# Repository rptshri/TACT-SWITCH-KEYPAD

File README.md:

# TACT-SWITCH-KEYPAD
KEYPAD USING TACT SWITCH A EAGLE SCHEMATICS AND BOARD,

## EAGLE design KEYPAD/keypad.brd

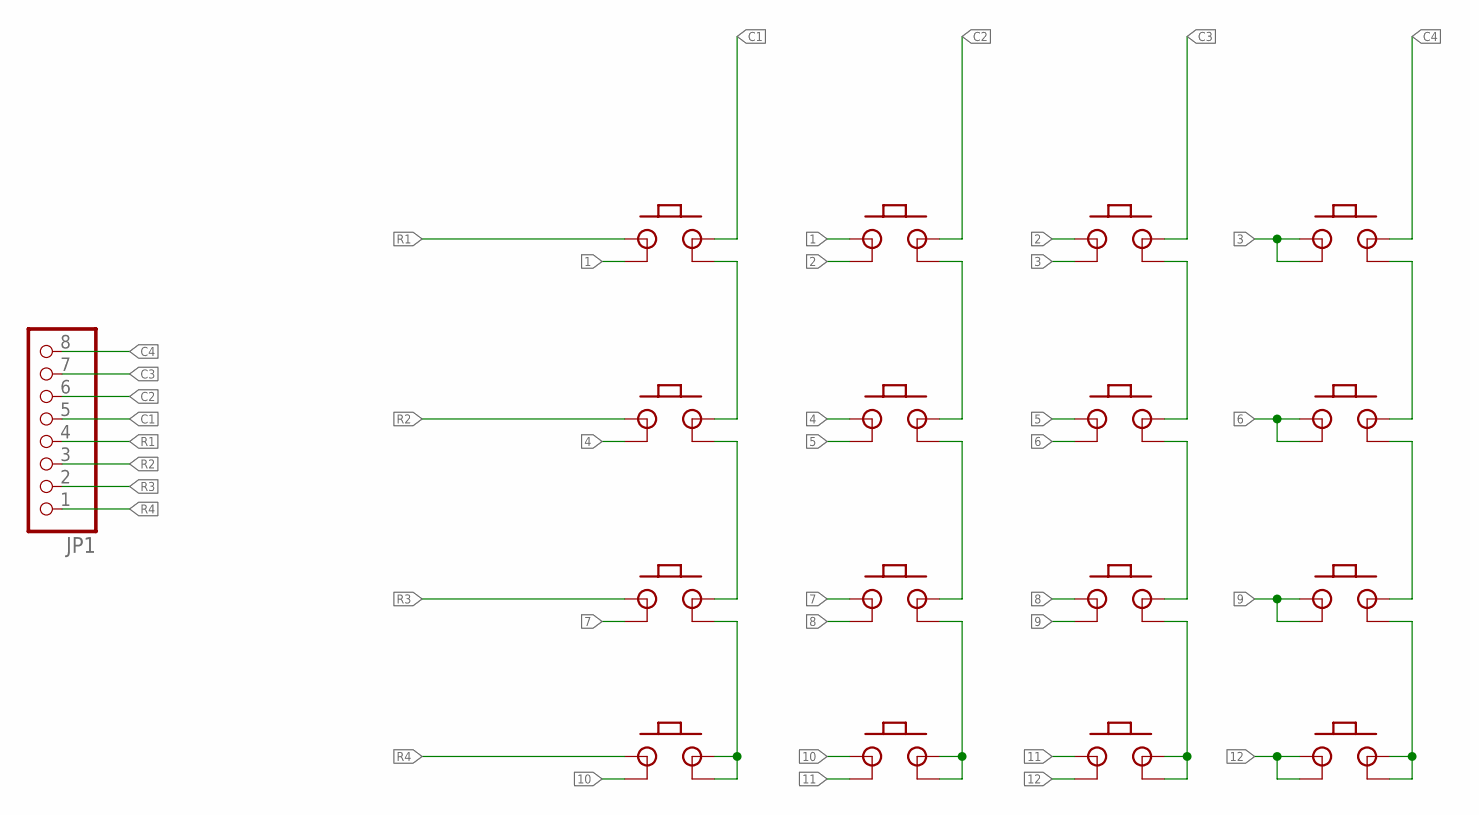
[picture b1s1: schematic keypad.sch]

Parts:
JP1: PINHD-1X8; 1X08
PB1, PB2, PB3, PB4, PB5, PB6, PB7, PB8, PB9, PB10, PB11, PB12, PB13, PB14, PB15, PB16: TACTSW

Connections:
1: PB1.P$2, PB2.P$1
2: PB2.P$2, PB3.P$1
3: PB3.P$2, PB4.P$1, PB4.P$2
4: PB5.P$2, PB6.P$1
5: PB6.P$2, PB7.P$1
6: PB7.P$2, PB8.P$1, PB8.P$2
7: PB9.P$2, PB10.P$1
8: PB10.P$2, PB11.P$1
9: PB7.P$4, PB11.P$2, PB11.P$3, PB12.P$1, PB12.P$2
10: PB13.P$2, PB14.P$1
11: PB14.P$2, PB15.P$1
12: PB15.P$2, PB16.P$1, PB16.P$2
C1: JP1.5, PB1.P$3
C2: JP1.6, PB2.P$3
C3: JP1.7, PB3.P$3
C4: JP1.8, PB4.P$3
unnamed: PB1.P$4, PB5.P$3
unnamed: PB5.P$4, PB9.P$3
unnamed: PB9.P$4, PB13.P$3, PB13.P$4
unnamed: PB2.P$4, PB6.P$3
unnamed: PB6.P$4, PB10.P$3
unnamed: PB10.P$4, PB14.P$3, PB14.P$4
unnamed: PB3.P$4, PB7.P$3
unnamed: PB11.P$4, PB15.P$3, PB15.P$4
unnamed: PB4.P$4, PB8.P$3
unnamed: PB8.P$4, PB12.P$3
unnamed: PB12.P$4, PB16.P$3, PB16.P$4
R1: JP1.4, PB1.P$1
R2: JP1.3, PB5.P$1
R3: JP1.2, PB9.P$1
R4: JP1.1, PB13.P$1

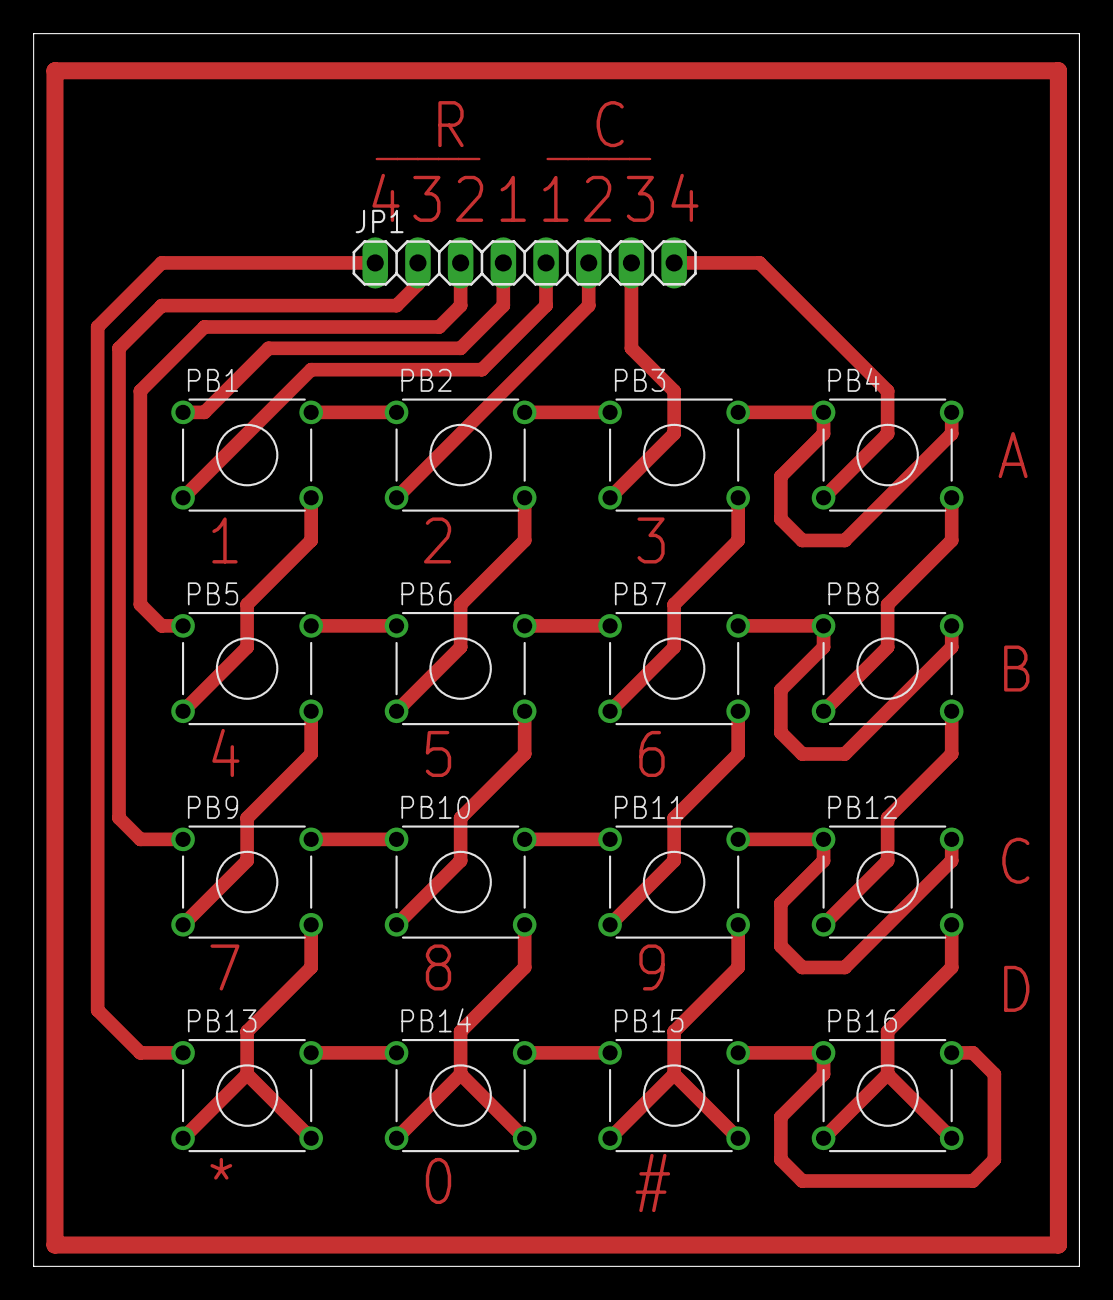
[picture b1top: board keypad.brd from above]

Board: 2 copper layers, 62.2 x 73.3 mm, 17 parts (0 on the bottom side), 31 nets.
